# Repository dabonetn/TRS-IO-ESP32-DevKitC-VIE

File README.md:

# TRS-IO

WORK IN PROGRESS

DO NOT USE YET!

TRS-IO gives a TRS-80 Model 1/III online capabilities and provides
access to a variety of services. TRS-IO currently features the
following capabilities:

1. Access to the <a href="https://retrostore.org">RetroStore</a>
2. <a href="http://frehd.com">FreHD</a> emulation
3. Access to files mounted on a SMB share or located on a micro-SD card
4. Access to remote servers via TCP
5. Virtual printer support

The TRS-IO versions for the Model 1 and Model III have some additional features that
are explained below. The following sections give an overview of TRS-IO as well as setup
instructions. This Github repository contains the complete source code
as well as the KiCad schematics for the PCB (Printed Circuit Board).
For the following descriptions it is assumed that an assembled TRS-IO
card is available.

### Overview

The figure below depicts the overall architecture. The TRS-80 machine
is connected to TRS-IO via the I/O bus.  TRS-IO has a WiFi module that
connects to the local WiFi router. This allows TRS-IO to connect to
the Internet and access various services. Note that TRS-IO can only
connect to a 2.4 GHz WiFi network. It is recommended to use an IPEX
antenna to improve WiFi reception.

### Prerequisites

TRS-IO requires a TRS-80 Model III with 48kB of RAM or a Model 1 with 16kB of RAM.
Floppy disk drives or a cassette tape are not required.

### Power Supply

There are two versions of TRS-IO that are tailored to the Model 1 and Model III. Each version makes use of an ESP32 microcontroller
as well as a Tang Nano 9K FPGA. Both the ESP32 microcontroller as well as the Nano 9K need to be powered. There are two ways of doing
this.

* Power each module independently via two USB cables that connect to the ESP32's micro-USB and the Nano 9K's USB-C connector.
  For this option, the "VU" jumper (mentioned below), <b>SHOULD NOT BE USED</b>.
* Power the ESP32 via the Nano 9K or vice versa. For this option, only one of the modules need to be provided with power. This option
  requires the "VU" jumper.
  
In the following, each variant of TRS-IO is explained in detail.

### TRS-IO for the Model III

The following figure shows the top view of the TRS-IO card for the Model III:

1. 50-pin I/O bus connector
2. High resolution graphics connector
3. 3.5mm audio jack
4. VU jumper
5. HDMI connector
6. Micro-SD card reader
7. Multi-color status LED
8. Micro-USB and USB-C connector
9. Status button

The TRS-IO card needs to be connected to the TRS-80 Model III's I/O
bus via a 50-pin ribbon cable (1). Furthermore, the TRS-IO card needs
a separate power supply via a standard 5V USB charger. Please refer
to the previous section regarding the power supply. The status button
(9) and the multi-color status LED (7) will be explained in the
configuration section. The micro-SD card reader is underneath the
Nano 9K module (6). The 3.5mm audio jack (3) can be connected to a standard
speaker for game sound and Orchestra 90 support. If the high resolution
connectors (2) are connected to the TRS-80, the HDMI connector (5) will
generate a video signal.

### TRS-IO for the Model 1

The following figure shows the top view of the TRS-IO card for the Model 1:

1. 40-pin I/O bus connector
2. Micro-SD card reader
3. HDMI connector
4. Micro-USB and USB-C connector
5. Multi-color status LED
6. Status button
7. VU jumper

The TRS-IO version for the Model 1 features a 40-pin connector that can
directly be connected via a ribbon cable to the I/O bus of a Model 1.
This version of TRS-IO offers the following features:

* HDMI signal of the M1's video screen that includes game sound.
* Upper 32kB RAM (emulated by the Nano 9K FPGA) for a total of 48kB of total RAM.
* 25ms heartbeat timer to trigger the realtime clock.
* FreHD auto-boot for an unmodified M1.

The HDMI connector (3) can be used instead of a CRT monitor. TRS-IO for the M1
also emulates the LE18 graphics cards. The color of the HDMI signal can
be set to white (X=0), green (X=1), and amber (X=2) via the following OUT statements:

```OUT 31,0:OUT 31,5:OUT 31,X```

Please refer to an earlier section on how to provide power to TRS-IO.

### Configuring TRS-IO

The core of the TRS-IO card is an ESP32 microcontroller that features
a WiFi module that is used to connect to a WiFi router. After
physically connecting the TRS-IO card to a TRS-80 Model 1/III as
explained in the previous sections, the WiFi module on the ESP32
microcontroller first needs to be be configured with the credentials
of the local WiFi network.

While in setup mode, the TRS-IO's status LED will continuously blink
in white to indicate that it has not yet been configured. While in
that mode, TRS-IO will create an open access point called
"TRS-IO". Use a laptop to connect to this WiFi network and then use a
browser to visit URL <a
href="http://trs-io.local">trs-io.local</a>. The following web page
should appear in the browser:

Some hosts do not correctly handle mDNS that is used to resolve <a
href="http://trs-io.local">trs-io.local</a>. In that case, visit the
IP address <a href="http://192.168.4.1">192.168.4.1</a> instead.
The web interface shown above can be used to configure SSID and password of the WiFi
network that TRS-IO should connect to, the local timezone as well as
the credentials of a SMB share. For open networks leave the WiFi
password field empty. Note that TRS-IO cannot connect to WiFi networks
that use a capture portal. The timezone as well as the SMB share are
not required but will result in limited functionality.

Once all the information is provided, click on submit to upload the
parameters. TRS-IO will automatically reboot and try to connect to the
specified WiFi network. If successful, the LED will turn green for a
few seconds. If the credentials are wrong or if the specified WiFi
network is not accessible, the LED light will turn permanently red.

Note that TRS-IO will store all parameters in its local flash memory,
so the setup only needs to be performed once. Once TRS-IO is connected
to a WiFi router, it should still be possible to access URL <a
href="http://trs-io.local">trs-io.local</a> from a browser on the same
WiFi network. If mDNS is not supported by the host, the following BASIC
program can be used to determine TRS-IO's local IP address that was
assigned by the router:

```
10 OUT 236,16
20 OUT31,0:OUT31,4
30 C=INP(31):IF C=0 THEN END
40 PRINT CHR$(C);
50 GOTO 30
```

The web interface will also display two icons to indicate the status
of the SMB share and the micro-SD card (see screenshot above). Green
icons indicate that TRS-IO has access. Red icons indicate an error.
In that case, hovering the mouse over the red icon will display the
error message. It should be noted that TRS-IO needs to be rebooted
whenever a micro-SD card is inserted or ejected.

Pushing the status button will make the LED flash twice. The first time for
the WiFi status (green: WiFi connected; red: WiFi not connected) and a
second time for the SMB status (green: connected to SMB share; red:
not connected to SMB share). With proper configuration parameters, the
LED should flash green twice. Holding down the push button for more
than three seconds will erase all configuration parameters and place
TRS-IO back into setup mode (status LED flashing white). This
might be necessary if TRS-IO is moved to a different WiFi network.

The status LED indicates the state of TRS-IO:

* Blinking white: TRS-IO is not configured. It will create an open WiFi access point named "TRS-IO"
* Solid green: when TRS-IO has been configured with WiFi credentials and TRS-IO was able
  to connect to the WiFi network, the status LED will light in solid green for several seconds.
* Solid red: TRS-IO was configured with WiFi credentials but it was not possible to connect to the specified
  network. The reason could be wrong credentials or the specified network is itself offline. The push button can be
  used to reset TRS-IO into setup mode in case different credentials need to be provided.
* Solid blue: TRS-IO performs an OTA (Over-the-Air) update. TRS-IO will automatically detect
  newer firmware versions and will download and install the new firmware. The status LED will light solid blue during
  this process.
* Off: the status LED will be off during regular operations when TRS-IO is connected to the specified
  WiFi network and ready to accept commands from the TRS-80 Model III.
 
### FreHD

TRS-IO is compatible with the popular <a
href="http://frehd.com">FreHD</a> hard disk emulator. The FreHD disk
images can either be stored on a SMB share or on a micro-SD card.
If a micro-SD card is inserted, it will take precedence over
a mounted SMB share. Once TRS-IO is configured to access a SMB share,
simply copy the required files such as <a
href="http://members.iinet.net.au/~ianmav/trs80/downloads.htm">FREHD.ROM</a>
to the SMB share. Alternatively, the disk images can be transferred
to the micro-SD card. The IMPORT/EXPORT utilities will access files on the
SMB share or micro-SD card respectively.

### Virtual Printer Interface

TRS-IO support a virtual printer interface. Visiting <a
href="http://trs-io.local/printer">trs-io.local/printer</a> from a browser
will open the printer interface. Any printer output from the M1/MIII will
be displayed in the printer interface. If the host cannot resolve the mDNS name
trs-io.local, the above BASIC program can be used to determine the TRS-80's
IP address.

 ### Launching the native RetroStore Client

The <a href="https://retrostore.org">RetroStore</a> hosts applications
for the Tandy Radio Shack vintage computers and allows to seamlessly
download and run these applications without the need of cassettes or
floppy disks. TRS-IO acts as a gateway to the <a
href="https://retrostore.org">RetroStore</a>. This requires to run a
program on the TRS-80 that interfaces with TRS-IO. This program is
available as a regular <a
href="https://github.com/apuder/TRS-IO/raw/master/src/esp/components/retrostore/rsclient.cmd">CMD</a>
executable.  For TRS-80 machines with attached physical floppy disks,
this CMD executable can be copied to a floppy disk and launched the
usual way. For TRS-80 machines that have neither floppy disk drives
nor cassette drives, it is also possible to bootstrap the native
client via the following short BASIC program:
 
 ```BASIC
 10 OUT236,16
 20 OUT31,3
 30 OUT31,1
 40 N=INP(31)+256*INP(31)
 50 FOR X=1 TO N:POKE20735+X,INP(31):NEXT
 RUN
 SYSTEM
 *? /20736
 ```
 
The above BASIC program will download the CMD executable from TRS-IO
and launch the native client.  Note that this procedure needs to be
repeated every time the TRS-80 is turned on.
 
### Using the native RetroStore Client

After successfully launching the native RetroStore client, the monitor
of the TRS-80 should look like this:

The screenshot above shows the main menu of the native RetroStore
client. The arrow indicates the currently selected menu item.  The up
and down cursor keys can be used to move between the various menu
items. Hitting the ENTER key will activate the currently selected
menu item. Pressing CLEAR or BREAK in sub-menus will return to the
previous menu.
 
Keyboard controls:
 
 * Cursor up/down: toggle menu selection
 * ENTER: select current menu selection
 * BREAK/CLEAR: exit to previous screen

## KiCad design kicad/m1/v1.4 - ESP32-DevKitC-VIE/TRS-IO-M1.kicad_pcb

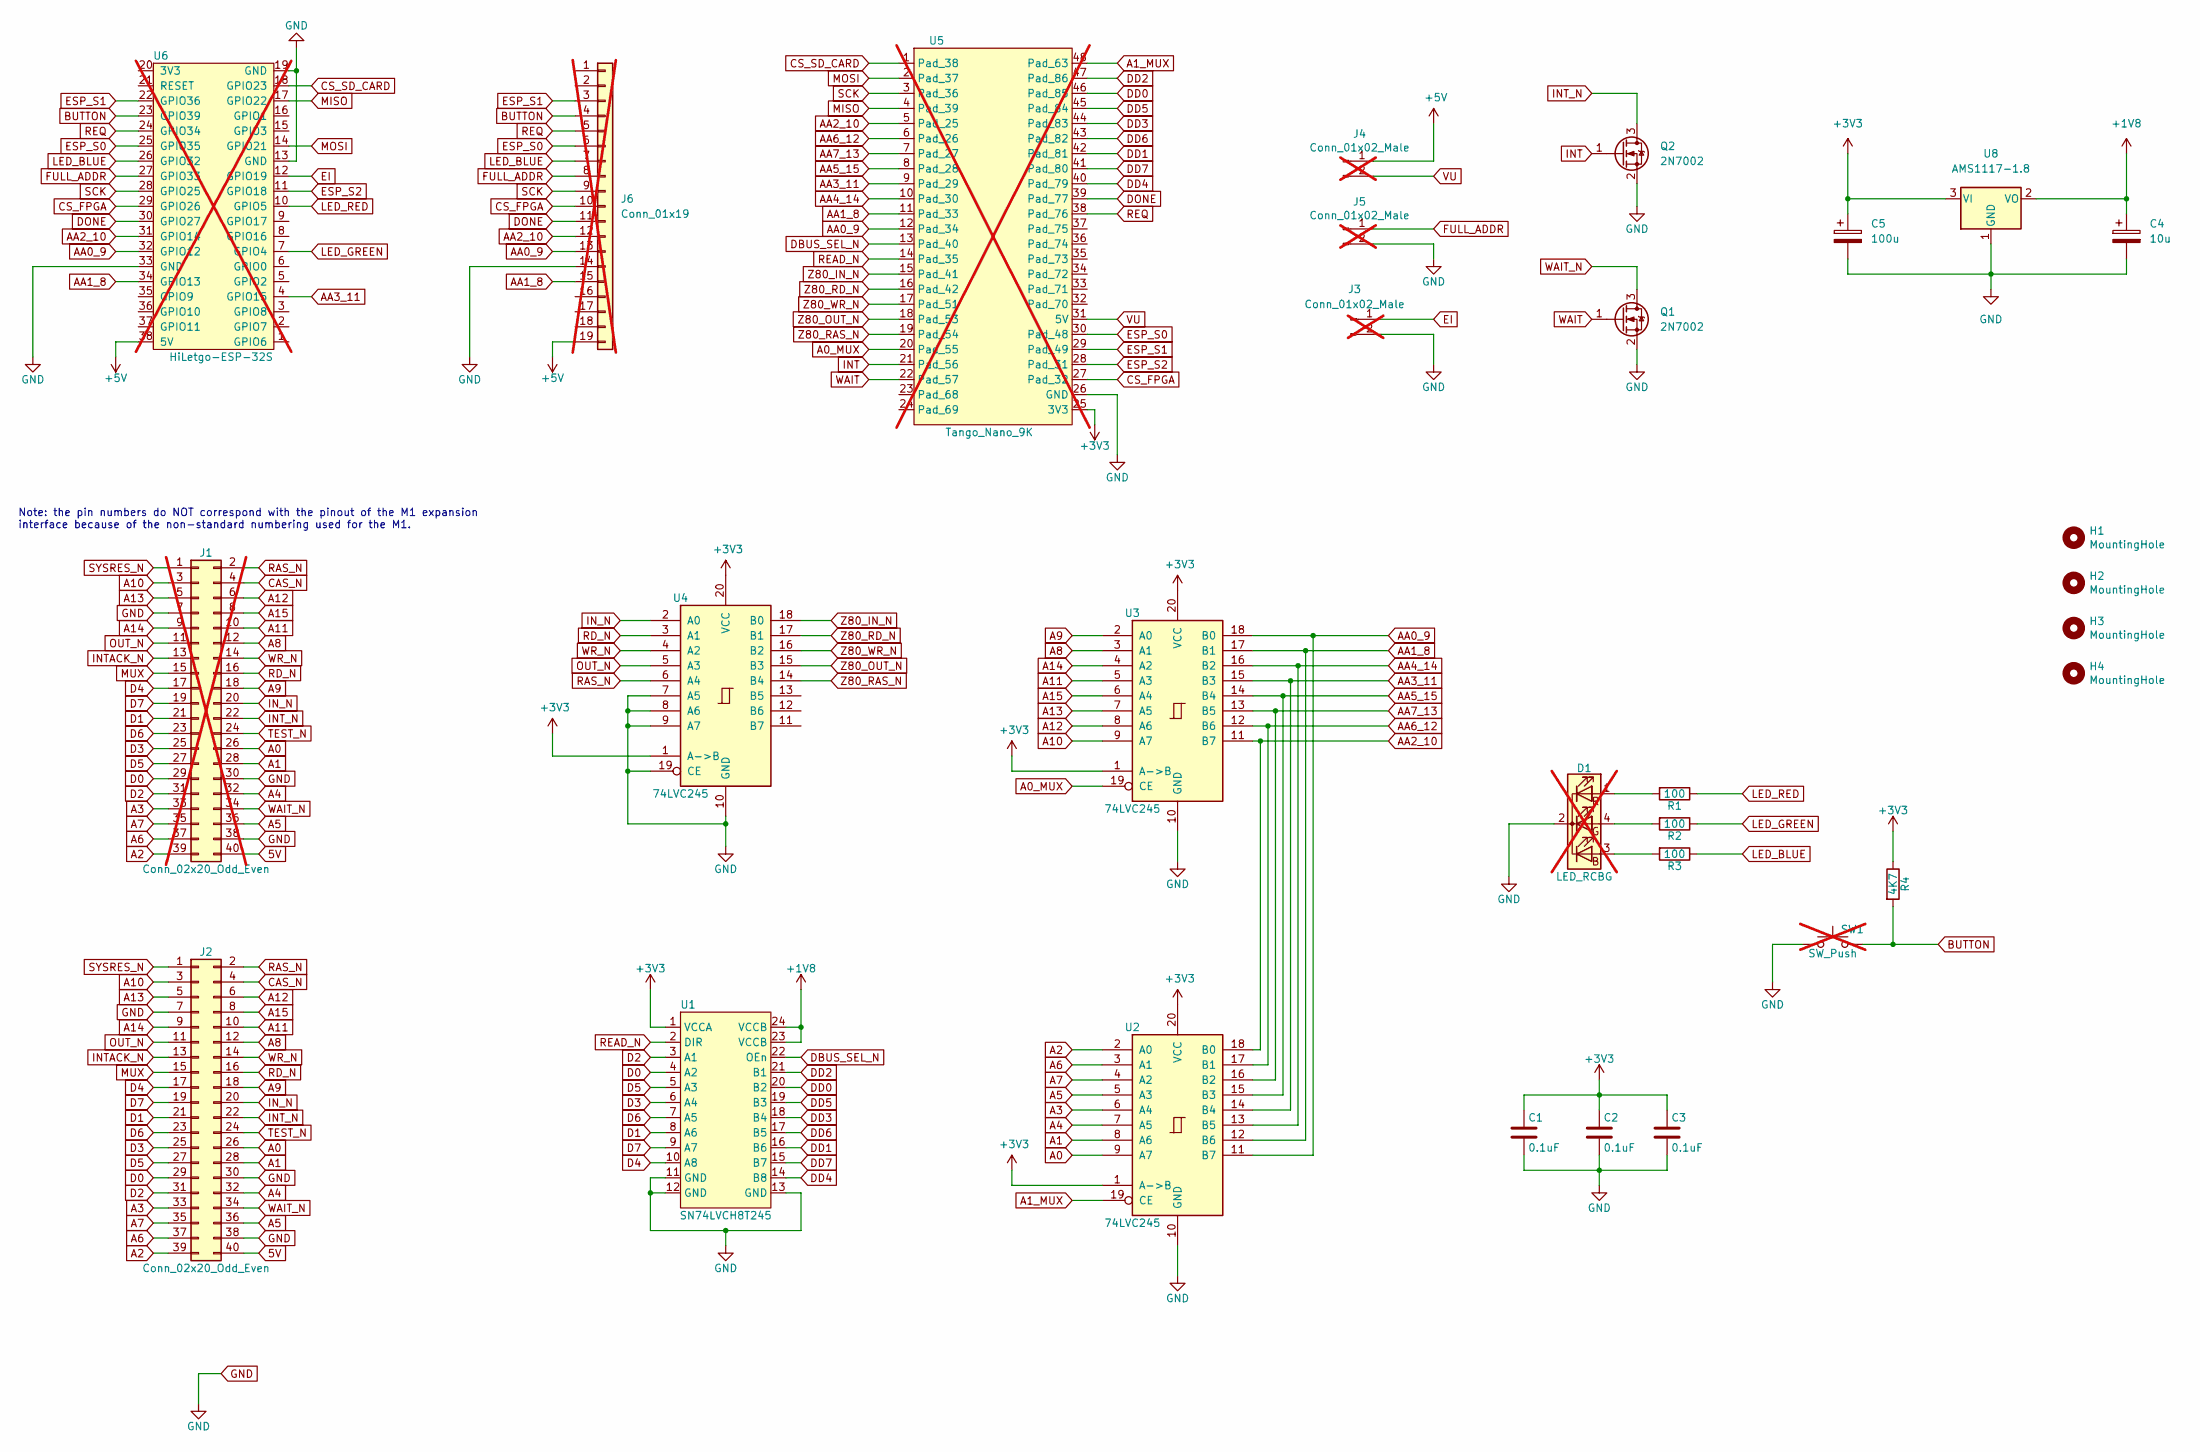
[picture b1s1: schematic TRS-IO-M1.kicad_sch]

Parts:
C1, C2, C3: 0.1uF; C_0805_2012Metric_Pad1.18x1.45mm_HandSolder
C4: 10u; C_1206_3216Metric_Pad1.33x1.80mm_HandSolder
C5: 100u; C_1206_3216Metric_Pad1.33x1.80mm_HandSolder
D1: LED_RCBG; LED_D5.0mm-4_RGB; not fitted
H1, H2, H3, H4: MountingHole; MountingHole_3mm_Pad_Via
J1: Conn_02x20_Odd_Even; PinHeader_2x20_P2.54mm_Vertical; not fitted
J2: Conn_02x20_Odd_Even; TRSEDGE
J3, J4, J5: Conn_01x02_Male; PinHeader_1x02_P2.54mm_Vertical; not fitted
J6: Conn_01x19; PinHeader_1x19_P2.54mm_Vertical; not fitted
Q1, Q2: 2N7002; SOT-23
R1, R2, R3: 100; R_0805_2012Metric_Pad1.20x1.40mm_HandSolder
R4: 4K7; R_0805_2012Metric_Pad1.20x1.40mm_HandSolder
SW1: SW_Push; SW_PUSH_6mm_H9.5mm; not fitted
U1: SN74LVCH8T245; TSSOP-24_4.4x7.8mm_P0.65mm
U2, U3, U4: 74LVC245; SSOP-20_5.3x7.2mm_P0.65mm_slim
U5: Tango_Nano_9K; DIP-48_W22.9mm; not fitted
U6: HiLetgo-ESP-32S; DIP-38_W22.9mm; not fitted
U8: AMS1117-1.8; SOT-223-3_TabPin2

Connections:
5V: J1.40, J2.40
+1V8: C4.1, U1.23 (VCCB), U1.24 (VCCB), U8.2 (VO)
+3V3: C1.1, C2.1, C3.1, C5.1, R4.1, U1.1 (VCCA), U2.1 (A->B), U2.20 (VCC), U3.1 (A->B), U3.20 (VCC), U4.1 (A->B), U4.20 (VCC), U5.25 (3V3), U8.3 (VI)
+5V: J4.1, J6.19, U6.38 (5V)
A0: J1.26, J2.26, U2.9 (A7)
A0_MUX: U3.19 (CE), U5.20 (Pad_55)
A1: J1.28, J2.28, U2.8 (A6)
A1_MUX: U2.19 (CE), U5.48 (Pad_63)
A2: J1.39, J2.39, U2.2 (A0)
A3: J1.33, J2.33, U2.6 (A4)
A4: J1.32, J2.32, U2.7 (A5)
A5: J1.36, J2.36, U2.5 (A3)
A6: J1.37, J2.37, U2.3 (A1)
A7: J1.35, J2.35, U2.4 (A2)
A8: J1.12, J2.12, U3.3 (A1)
A9: J1.18, J2.18, U3.2 (A0)
A10: J1.3, J2.3, U3.9 (A7)
A11: J1.10, J2.10, U3.5 (A3)
A12: J1.6, J2.6, U3.8 (A6)
A13: J1.5, J2.5, U3.7 (A5)
A14: J1.9, J2.9, U3.4 (A2)
A15: J1.8, J2.8, U3.6 (A4)
AA0_9: J6.13, U2.11 (B7), U3.18 (B0), U5.12 (Pad_34), U6.32 (GPIO12)
AA1_8: J6.15, U2.12 (B6), U3.17 (B1), U5.11 (Pad_33), U6.34 (GPIO13)
AA2_10: J6.12, U2.18 (B0), U3.11 (B7), U5.5 (Pad_25), U6.31 (GPIO14)
AA3_11: U2.14 (B4), U3.15 (B3), U5.9 (Pad_29), U6.4 (GPIO15)
AA4_14: U2.13 (B5), U3.16 (B2), U5.10 (Pad_30)
AA5_15: U2.15 (B3), U3.14 (B4), U5.8 (Pad_28)
AA6_12: U2.17 (B1), U3.12 (B6), U5.6 (Pad_26)
AA7_13: U2.16 (B2), U3.13 (B5), U5.7 (Pad_27)
BUTTON: J6.4, R4.2, SW1.2, U6.23 (GPIO39)
CAS_N: J1.4, J2.4
CS_FPGA: J6.10, U5.27 (Pad_32), U6.29 (GPIO26)
CS_SD_CARD: U5.1 (Pad_38), U6.18 (GPIO23)
D0: J1.29, J2.29, U1.4 (A2)
D1: J1.21, J2.21, U1.8 (A6)
D2: J1.31, J2.31, U1.3 (A1)
D3: J1.25, J2.25, U1.6 (A4)
D4: J1.17, J2.17, U1.10 (A8)
D5: J1.27, J2.27, U1.5 (A3)
D6: J1.23, J2.23, U1.7 (A5)
D7: J1.19, J2.19, U1.9 (A7)
DBUS_SEL_N: U1.22 (OEn), U5.13 (Pad_40)
DD0: U1.20 (B2), U5.46 (Pad_85)
DD1: U1.16 (B6), U5.42 (Pad_81)
DD2: U1.21 (B1), U5.47 (Pad_86)
DD3: U1.18 (B4), U5.44 (Pad_83)
DD4: U1.14 (B8), U5.40 (Pad_79)
DD5: U1.19 (B3), U5.45 (Pad_84)
DD6: U1.17 (B5), U5.43 (Pad_82)
DD7: U1.15 (B7), U5.41 (Pad_80)
DONE: J6.11, U5.39 (Pad_77), U6.30 (GPIO27)
EI: J3.1, U6.12 (GPIO19)
ESP_S0: J6.6, U5.30 (Pad_48), U6.25 (GPIO35)
ESP_S1: J6.3, U5.29 (Pad_49), U6.22 (GPIO36)
ESP_S2: U5.28 (Pad_31), U6.11 (GPIO18)
FULL_ADDR: J5.1, J6.8, U6.27 (GPIO33)
GND: C1.2, C2.2, C3.2, C4.2, C5.2, D1.2 (K), J1.7, J1.30, J1.38, J2.7, J2.30, J2.38, J3.2, J5.2, J6.14, Q1.2 (S), Q2.2 (S), SW1.1, U1.11 (GND), U1.12 (GND), U1.13 (GND), U2.10 (GND), U3.10 (GND), U4.7 (A5), U4.8 (A6), U4.9 (A7), U4.10 (GND), U4.19 (CE), U5.26 (GND), U6.13 (GND), U6.19 (GND), U6.33 (GND), U8.1 (GND)
INT: Q2.1 (G), U5.21 (Pad_56)
INTACK_N: J1.13, J2.13
INT_N: J1.22, J2.22, Q2.3 (D)
IN_N: J1.20, J2.20, U4.2 (A0)
LED_BLUE: J6.7, R3.1, U6.26 (GPIO32)
LED_GREEN: R2.1, U6.7 (GPIO4)
LED_RED: R1.1, U6.10 (GPIO5)
MISO: U5.4 (Pad_39), U6.17 (GPIO22)
MOSI: U5.2 (Pad_37), U6.14 (GPIO21)
MUX: J1.15, J2.15
unnamed: D1.3 (BA), R3.2
unnamed: D1.4 (GA), R2.2
unnamed: D1.1 (RA), R1.2
OUT_N: J1.11, J2.11, U4.5 (A3)
RAS_N: J1.2, J2.2, U4.6 (A4)
RD_N: J1.16, J2.16, U4.3 (A1)
READ_N: U1.2 (DIR), U5.14 (Pad_35)
REQ: J6.5, U5.38 (Pad_76), U6.24 (GPIO34)
SCK: J6.9, U5.3 (Pad_36), U6.28 (GPIO25)
SYSRES_N: J1.1, J2.1
TEST_N: J1.24, J2.24
VU: J4.2, U5.31 (5V)
WAIT: Q1.1 (G), U5.22 (Pad_57)
WAIT_N: J1.34, J2.34, Q1.3 (D)
WR_N: J1.14, J2.14, U4.4 (A2)
Z80_IN_N: U4.18 (B0), U5.15 (Pad_41)
Z80_OUT_N: U4.15 (B3), U5.18 (Pad_53)
Z80_RAS_N: U4.14 (B4), U5.19 (Pad_54)
Z80_RD_N: U4.17 (B1), U5.16 (Pad_42)
Z80_WR_N: U4.16 (B2), U5.17 (Pad_51)

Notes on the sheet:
Note: the pin numbers do NOT correspond with the pinout of the M1 expansion interface because of the non-standard numbering used for the M1.

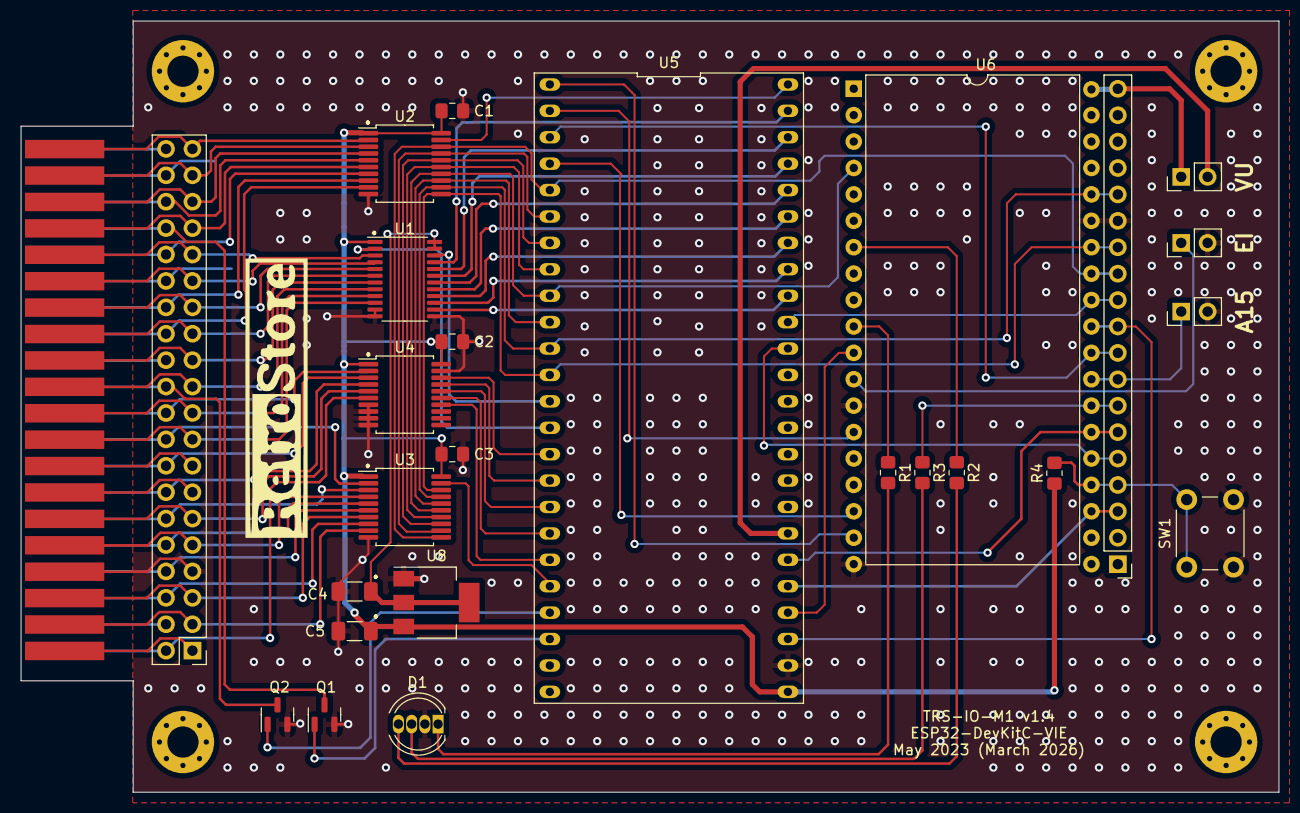
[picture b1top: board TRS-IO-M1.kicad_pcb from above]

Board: 2 copper layers, 121.0 x 74.2 mm, 31 parts (0 on the bottom side), 88 nets.

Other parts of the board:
G1: LOGO

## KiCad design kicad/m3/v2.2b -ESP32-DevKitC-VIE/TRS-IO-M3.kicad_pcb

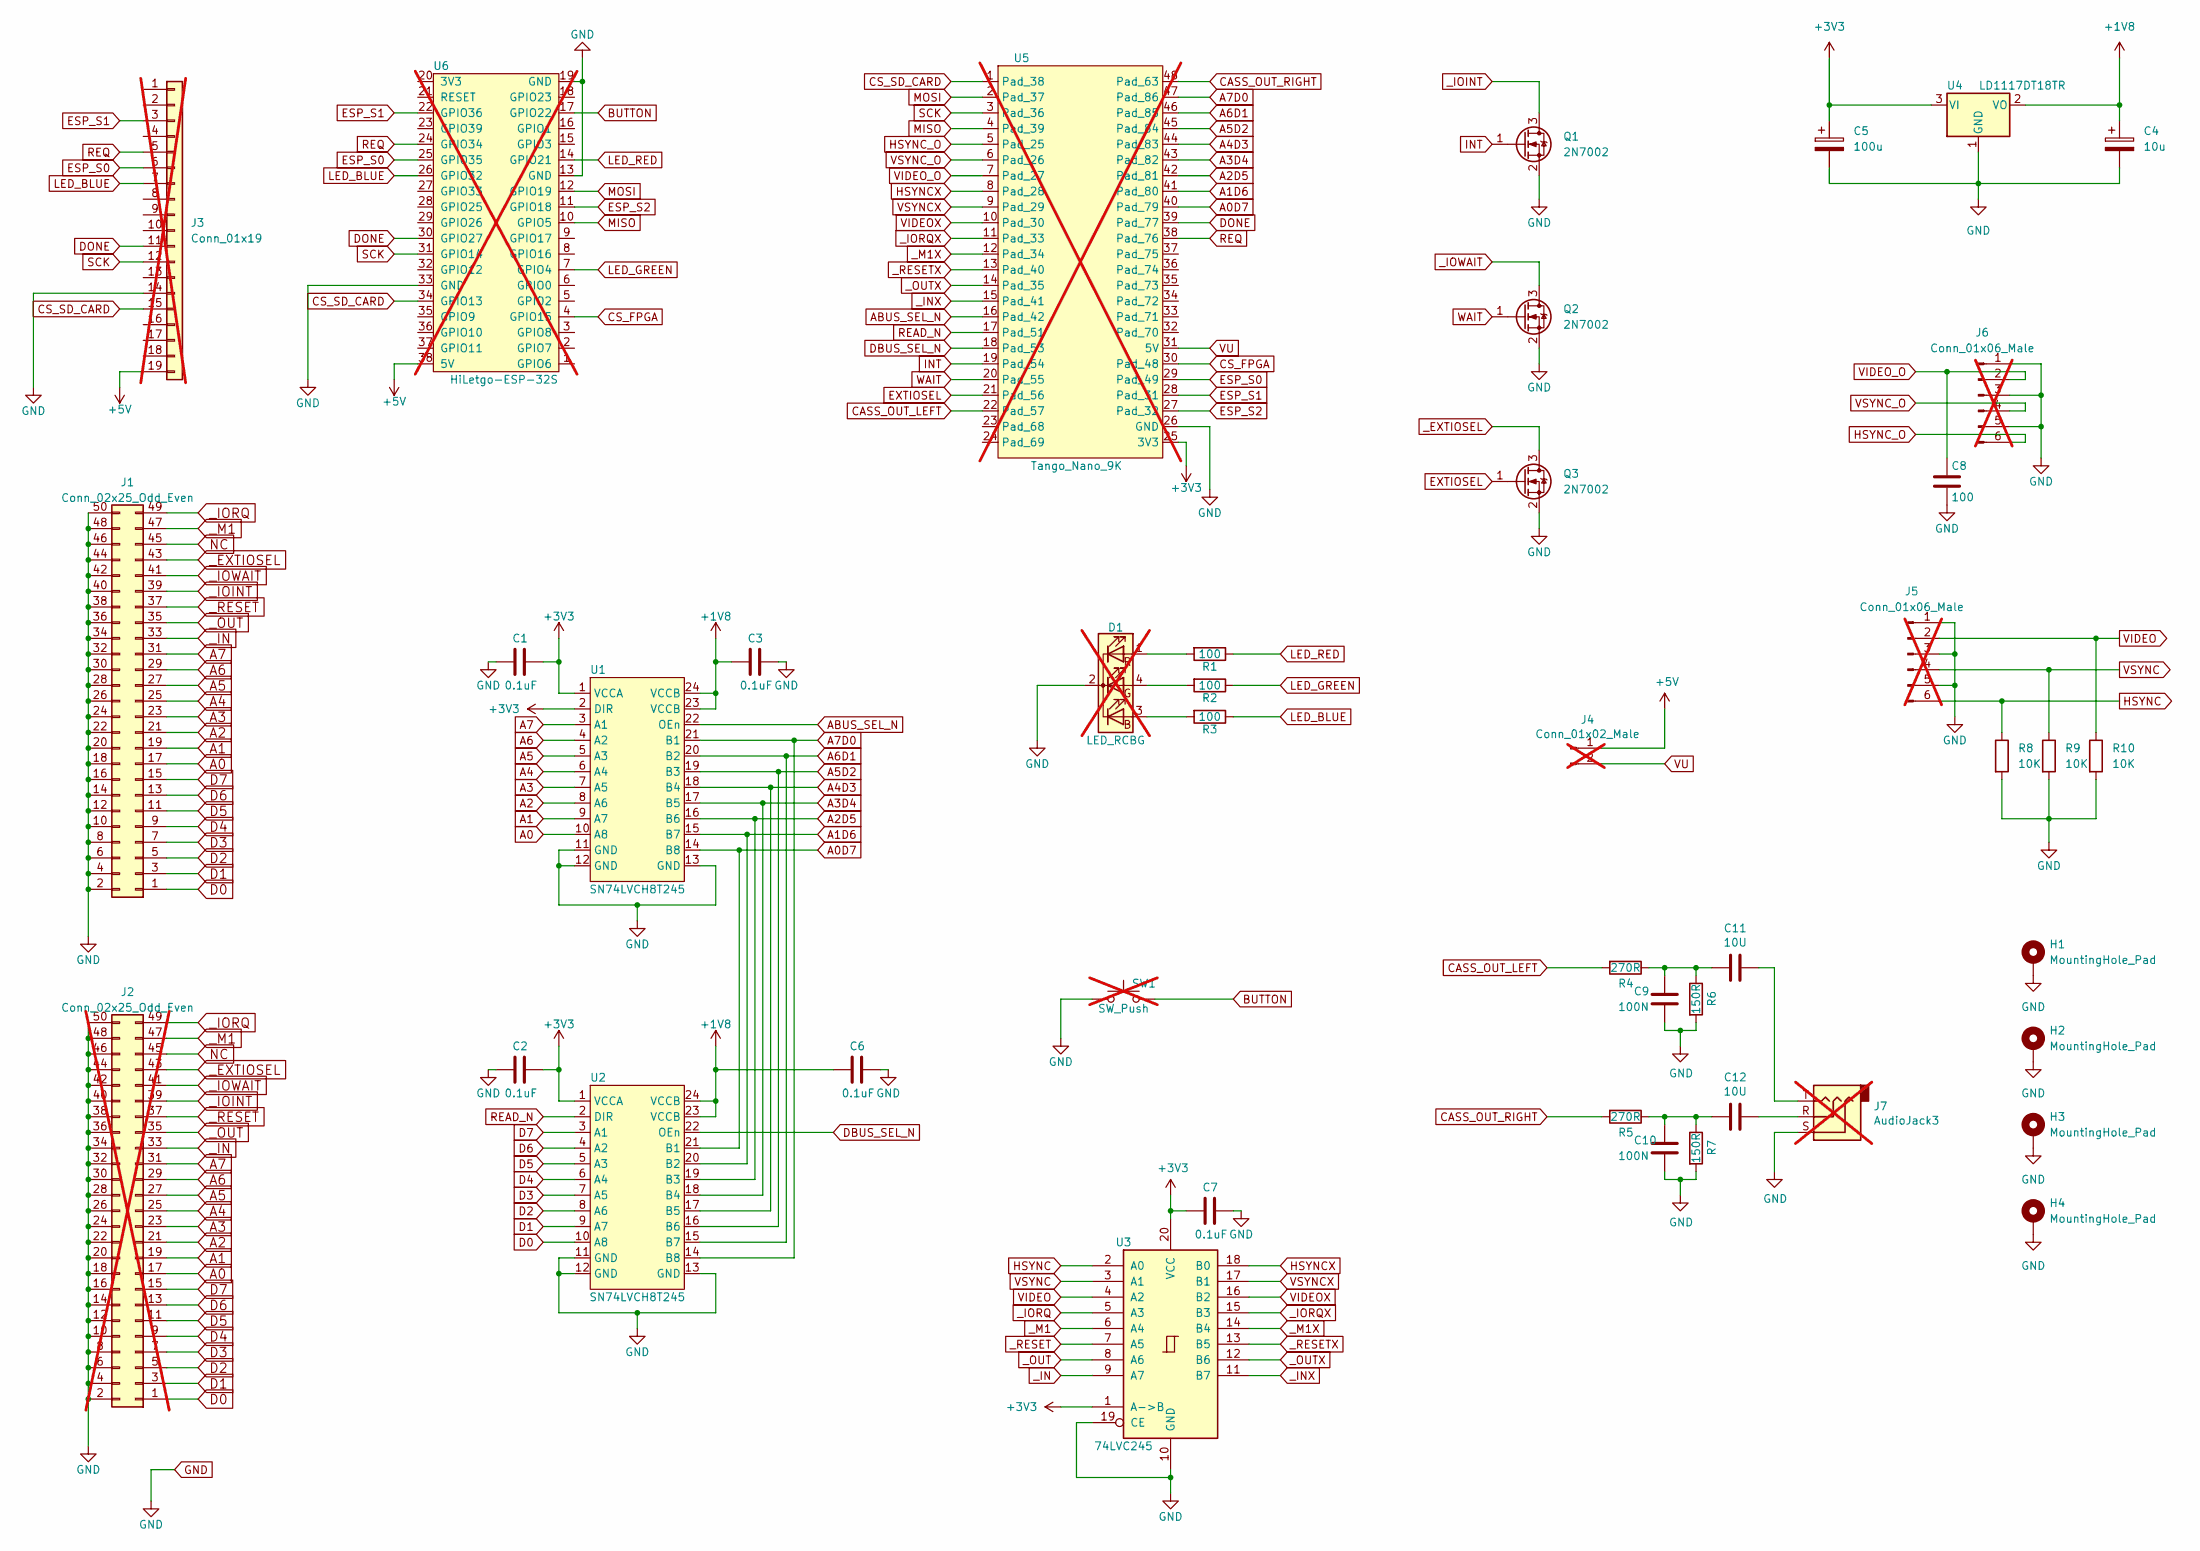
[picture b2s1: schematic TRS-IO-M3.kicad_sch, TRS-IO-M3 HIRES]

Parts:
C1, C2, C3, C6, C7: 0.1uF; C_0805_2012Metric_Pad1.18x1.45mm_HandSolder
C4: 10u; C_1206_3216Metric_Pad1.33x1.80mm_HandSolder
C5: 100u; C_1206_3216Metric_Pad1.33x1.80mm_HandSolder
C8: 100; C_0805_2012Metric_Pad1.18x1.45mm_HandSolder
C9, C10: 100N; C_0805_2012Metric_Pad1.18x1.45mm_HandSolder
C11, C12: 10U; C_1206_3216Metric_Pad1.33x1.80mm_HandSolder
D1: LED_RCBG; LED_D5.0mm-4_RGB; not fitted
H1, H2, H3, H4: MountingHole_Pad; MountingHole_3mm_Pad_Via
J1: Conn_02x25_Odd_Even; EDGE50
J2: Conn_02x25_Odd_Even; Pin_Header_Straight_2x25_Pitch2.54mm; not fitted
J3: Conn_01x19; PinHeader_1x19_P2.54mm_Vertical; not fitted
J4: Conn_01x02_Male; PinHeader_1x02_P2.54mm_Vertical; not fitted
J5, J6: Conn_01x06_Male; PinHeader_1x06_P2.54mm_Horizontal; not fitted
J7: AudioJack3; Jack_3.5mm_CUI_SJ1-3535NG_Horizontal_CircularHoles; not fitted
Q1, Q2, Q3: 2N7002; SOT-23
R1, R2, R3: 100; R_0805_2012Metric_Pad1.20x1.40mm_HandSolder
R4, R5: 270R; R_0805_2012Metric_Pad1.20x1.40mm_HandSolder
R6, R7: 150R; R_0805_2012Metric_Pad1.20x1.40mm_HandSolder
R8, R9, R10: 10K; R_0805_2012Metric_Pad1.20x1.40mm_HandSolder
SW1: SW_Push; SW_PUSH_6mm_H9.5mm; not fitted
U1, U2: SN74LVCH8T245; TSSOP-24_4.4x7.8mm_P0.65mm
U3: 74LVC245; SSOP-20_5.3x7.2mm_P0.65mm_slim
U4: LD1117DT18TR; TO-252-3_TabPin2
U5: Tango_Nano_9K; DIP-48_W22.9mm; not fitted
U6: HiLetgo-ESP-32S; DIP-38_W22.9mm; not fitted

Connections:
+1V8: C3.2, C4.1, C6.2, U1.23 (VCCB), U1.24 (VCCB), U2.23 (VCCB), U2.24 (VCCB), U4.2 (VO)
+3V3: C1.1, C2.1, C5.1, C7.2, U1.1 (VCCA), U1.2 (DIR), U2.1 (VCCA), U3.1 (A->B), U3.20 (VCC), U4.3 (VI), U5.25 (3V3)
+5V: J3.19, J4.1, U6.38 (5V)
A0: J1.17, J2.17, U1.10 (A8)
A0D7: U1.14 (B8), U2.21 (B1), U5.40 (Pad_79)
A1: J1.19, J2.19, U1.9 (A7)
A1D6: U1.15 (B7), U2.20 (B2), U5.41 (Pad_80)
A2: J1.21, J2.21, U1.8 (A6)
A2D5: U1.16 (B6), U2.19 (B3), U5.42 (Pad_81)
A3: J1.23, J2.23, U1.7 (A5)
A3D4: U1.17 (B5), U2.18 (B4), U5.43 (Pad_82)
A4: J1.25, J2.25, U1.6 (A4)
A4D3: U1.18 (B4), U2.17 (B5), U5.44 (Pad_83)
A5: J1.27, J2.27, U1.5 (A3)
A5D2: U1.19 (B3), U2.16 (B6), U5.45 (Pad_84)
A6: J1.29, J2.29, U1.4 (A2)
A6D1: U1.20 (B2), U2.15 (B7), U5.46 (Pad_85)
A7: J1.31, J2.31, U1.3 (A1)
A7D0: U1.21 (B1), U2.14 (B8), U5.47 (Pad_86)
ABUS_SEL_N: U1.22 (OEn), U5.16 (Pad_42)
BUTTON: SW1.2, U6.17 (GPIO22)
CASS_OUT_LEFT: R4.2, U5.22 (Pad_57)
CASS_OUT_RIGHT: R5.2, U5.48 (Pad_63)
CS_FPGA: U5.30 (Pad_48), U6.4 (GPIO15)
CS_SD_CARD: J3.15, U5.1 (Pad_38), U6.34 (GPIO13)
D0: J1.1, J2.1, U2.10 (A8)
D1: J1.3, J2.3, U2.9 (A7)
D2: J1.5, J2.5, U2.8 (A6)
D3: J1.7, J2.7, U2.7 (A5)
D4: J1.9, J2.9, U2.6 (A4)
D5: J1.11, J2.11, U2.5 (A3)
D6: J1.13, J2.13, U2.4 (A2)
D7: J1.15, J2.15, U2.3 (A1)
DBUS_SEL_N: U2.22 (OEn), U5.18 (Pad_53)
DONE: J3.11, U5.39 (Pad_77), U6.30 (GPIO27)
ESP_S0: J3.6, U5.29 (Pad_49), U6.25 (GPIO35)
ESP_S1: J3.3, U5.28 (Pad_31), U6.22 (GPIO36)
ESP_S2: U5.27 (Pad_32), U6.11 (GPIO18)
EXTIOSEL: Q3.1 (G), U5.21 (Pad_56)
GND: C1.2, C2.2, C3.1, C4.2, C5.2, C6.1, C7.1, C8.2, C9.2, C10.2, D1.2 (K), H1.1, H2.1, H3.1, H4.1, J1.2, J1.4, J1.6, J1.8, J1.10, J1.12, J1.14, J1.16, J1.18, J1.20, J1.22, J1.24, J1.26, J1.28, J1.30, J1.32, J1.34, J1.36, J1.38, J1.40, J1.42, J1.44, J1.46, J1.48, J1.50, J2.2, J2.4, J2.6, J2.8, J2.10, J2.12, J2.14, J2.16, J2.18, J2.20, J2.22, J2.24, J2.26, J2.28, J2.30, J2.32, J2.34, J2.36, J2.38, J2.40, J2.42, J2.44, J2.46, J2.48, J2.50, J3.14, J5.1, J5.3, J5.5, J6.1, J6.3, J6.5, J7.S, Q1.2 (S), Q2.2 (S), Q3.2 (S), R6.2, R7.2, R8.2, R9.2, R10.2, SW1.1, U1.11 (GND), U1.12 (GND), U1.13 (GND), U2.11 (GND), U2.12 (GND), U2.13 (GND), U3.10 (GND), U3.19 (CE), U4.1 (GND), U5.26 (GND), U6.13 (GND), U6.19 (GND), U6.33 (GND)
HSYNC: J5.6, R8.1, U3.2 (A0)
HSYNCX: U3.18 (B0), U5.8 (Pad_28)
HSYNC_O: J6.6, U5.5 (Pad_25)
INT: Q1.1 (G), U5.19 (Pad_54)
LED_BLUE: J3.7, R3.1, U6.26 (GPIO32)
LED_GREEN: R2.1, U6.7 (GPIO4)
LED_RED: R1.1, U6.14 (GPIO21)
MISO: U5.4 (Pad_39), U6.10 (GPIO5)
MOSI: U5.2 (Pad_37), U6.12 (GPIO19)
NC: J1.45, J2.45
unnamed: C10.1, C12.2, R5.1, R7.1
unnamed: C11.1, J7.T
unnamed: C9.1, C11.2, R4.1, R6.1
unnamed: C12.1, J7.R
unnamed: D1.3 (BA), R3.2
unnamed: D1.4 (GA), R2.2
unnamed: D1.1 (RA), R1.2
READ_N: U2.2 (DIR), U5.17 (Pad_51)
REQ: J3.5, U5.38 (Pad_76), U6.24 (GPIO34)
SCK: J3.12, U5.3 (Pad_36), U6.31 (GPIO14)
VIDEO: J5.2, R10.1, U3.4 (A2)
VIDEOX: U3.16 (B2), U5.10 (Pad_30)
VIDEO_O: C8.1, J6.2, U5.7 (Pad_27)
VSYNC: J5.4, R9.1, U3.3 (A1)
VSYNCX: U3.17 (B1), U5.9 (Pad_29)
VSYNC_O: J6.4, U5.6 (Pad_26)
VU: J4.2, U5.31 (5V)
WAIT: Q2.1 (G), U5.20 (Pad_55)
_EXTIOSEL: J1.43, J2.43, Q3.3 (D)
_IN: J1.33, J2.33, U3.9 (A7)
_INX: U3.11 (B7), U5.15 (Pad_41)
_IOINT: J1.39, J2.39, Q1.3 (D)
_IORQ: J1.49, J2.49, U3.5 (A3)
_IORQX: U3.15 (B3), U5.11 (Pad_33)
_IOWAIT: J1.41, J2.41, Q2.3 (D)
_M1: J1.47, J2.47, U3.6 (A4)
_M1X: U3.14 (B4), U5.12 (Pad_34)
_OUT: J1.35, J2.35, U3.8 (A6)
_OUTX: U3.12 (B6), U5.14 (Pad_35)
_RESET: J1.37, J2.37, U3.7 (A5)
_RESETX: U3.13 (B5), U5.13 (Pad_40)

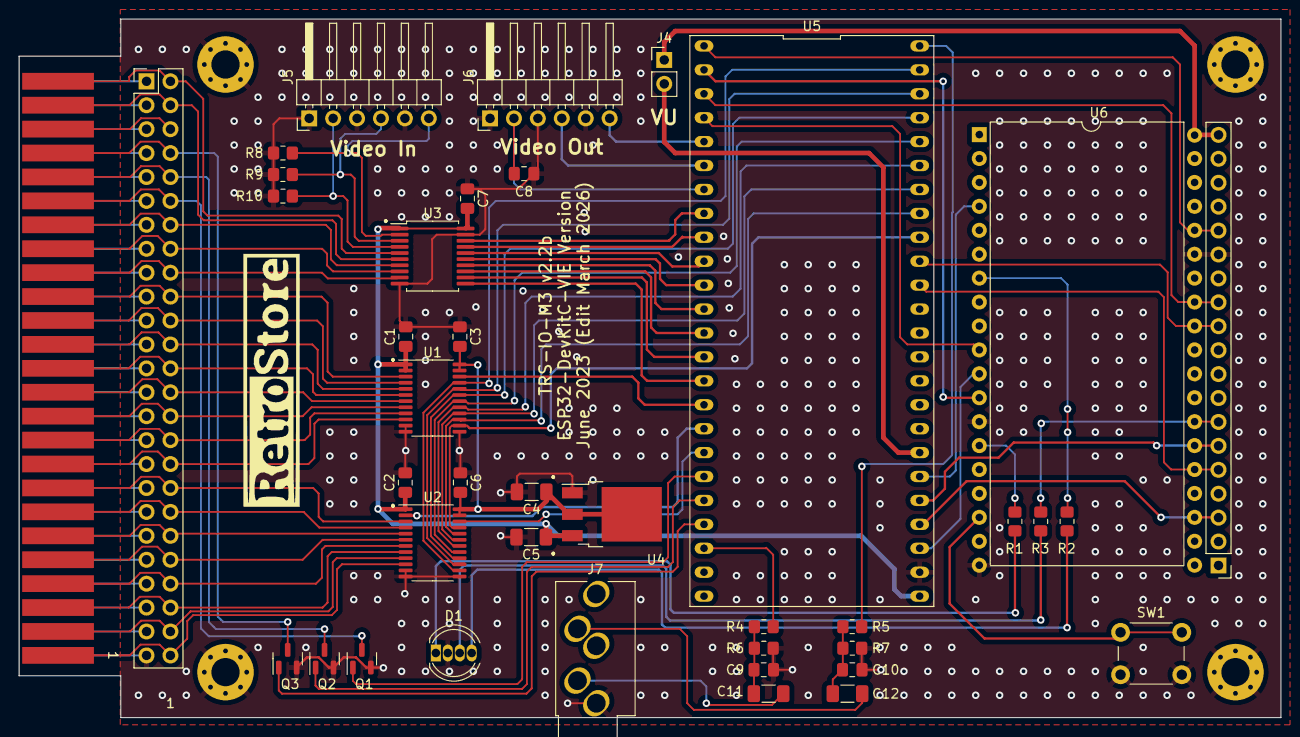
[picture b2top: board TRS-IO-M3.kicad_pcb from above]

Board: 2 copper layers, 134.0 x 74.2 mm, 45 parts (0 on the bottom side), 81 nets.

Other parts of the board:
G1: LOGO

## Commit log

2026-03-10 First changes upload
    Changed boards to support GPIOs 35 & 36, no gerbers yet.
    Changed source code for flash size, and gpio pins.
2026-03-10 added gerbers
2026-03-28 Web Page Edit
